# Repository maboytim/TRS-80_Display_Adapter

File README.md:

# TRS-80_Display_Adapter
Display board and CRT replacement for TRS-80 Models 3 and 4 and the big Tandy's.

### Overview

The adapter board connects to where the the display board normally connects.  It converts the video signals to HDMI or VGA so a modern monitor can be used instead of the builtin CRT.  The adapter uses a low cost (~$15) Nano-9k FPGA module.

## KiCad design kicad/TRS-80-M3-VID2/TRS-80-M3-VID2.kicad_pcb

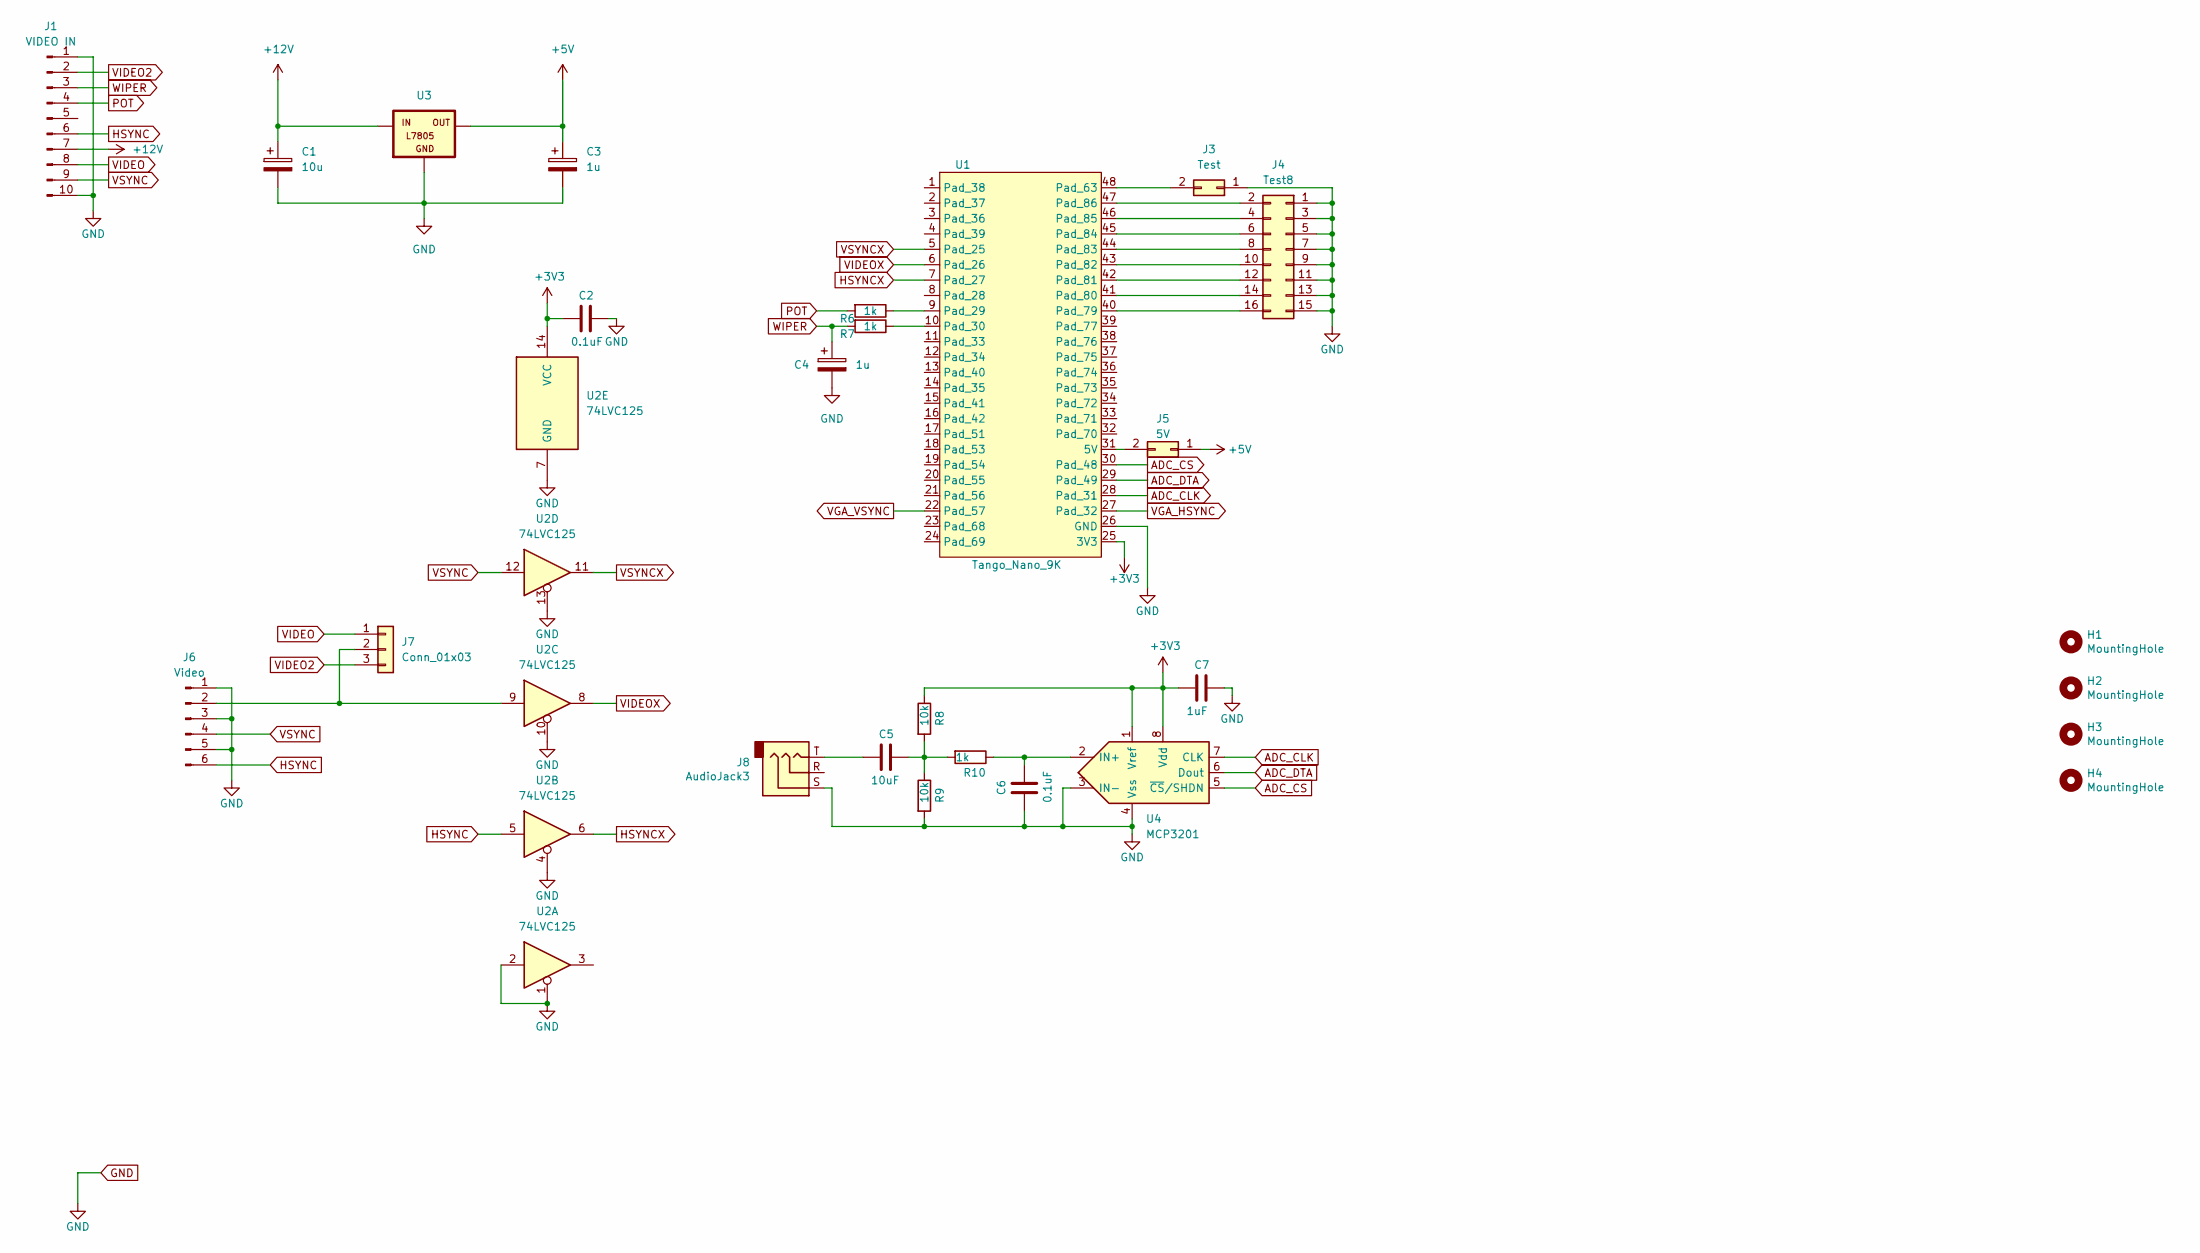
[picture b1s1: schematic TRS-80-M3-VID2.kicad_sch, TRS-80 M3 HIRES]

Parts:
C1: 10u; C_1206_3216Metric_Pad1.33x1.80mm_HandSolder
C2, C6: 0.1uF; C_0805_2012Metric_Pad1.18x1.45mm_HandSolder
C3, C4: 1u; C_1206_3216Metric_Pad1.33x1.80mm_HandSolder
C5: 10uF; C_0805_2012Metric_Pad1.18x1.45mm_HandSolder
C7: 1uF; C_0805_2012Metric_Pad1.18x1.45mm_HandSolder
H1, H2, H3, H4: MountingHole; MountingHole_3mm_Pad_Via
J1: VIDEO IN; TRSVID10
J3: Test; PinHeader_1x02_P2.54mm_Vertical
J4: Test8; PinSocket_2x08_P2.54mm_Vertical
J5: 5V; PinHeader_1x02_P2.54mm_Vertical
J6: Video; PinHeader_1x06_P2.54mm_Vertical
J7: Conn_01x03; PinHeader_1x03_P2.54mm_Vertical
J8: AudioJack3; Jack_3.5mm_CUI_SJ1-3535NG_Horizontal
R6, R7, R10: 1k; R_0805_2012Metric_Pad1.20x1.40mm_HandSolder
R8, R9: 10k; R_0805_2012Metric_Pad1.20x1.40mm_HandSolder
U1: Tango_Nano_9K; DIP-48_W22.9mm
U2: 74LVC125; SO-14_3.9x8.65mm_P1.27mm
U3: L7805; 78XXL
U4: MCP3201; SOIC-8_3.9x4.9mm_P1.27mm

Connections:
+3V3: C2.2, C7.2, R8.1, U1.25 (3V3), U2.14 (VCC), U4.1 (Vref), U4.8 (Vdd)
+5V: C3.1, J5.1, U3.OUT
+12V: C1.1, J1.7, U3.IN
ADC_CLK: U1.28 (Pad_31), U4.7 (CLK)
ADC_CS: U1.30 (Pad_48), U4.5 (~CS/SHDN)
ADC_DTA: U1.29 (Pad_49), U4.6 (Dout)
GND: C1.2, C2.1, C3.2, C4.2, C6.2, C7.1, J1.1, J1.10, J3.1, J4.1, J4.3, J4.5, J4.7, J4.9, J4.11, J4.13, J4.15, J6.1, J6.3, J6.5, J8.S, R9.2, U1.26 (GND), U2.1, U2.2, U2.4, U2.7 (GND), U2.10, U2.13, U3.GND, U4.3 (IN-), U4.4 (Vss)
HSYNC: J1.6, J6.6, U2.5
HSYNCX: U1.7 (Pad_27), U2.6
unnamed: C5.1, R8.2, R9.1, R10.2
unnamed: C5.2, J8.T
unnamed: J3.2, U1.48 (Pad_63)
unnamed: J4.2, U1.47 (Pad_86)
unnamed: J4.4, U1.46 (Pad_85)
unnamed: J4.6, U1.45 (Pad_84)
unnamed: J4.8, U1.44 (Pad_83)
unnamed: J4.10, U1.43 (Pad_82)
unnamed: J4.12, U1.42 (Pad_81)
unnamed: J4.14, U1.41 (Pad_80)
unnamed: J4.16, U1.40 (Pad_79)
unnamed: J5.2, U1.31 (5V)
unnamed: J6.2, J7.2, U2.9
unnamed: R6.1, U1.9 (Pad_29)
unnamed: R7.1, U1.10 (Pad_30)
unnamed: C6.1, R10.1, U4.2 (IN+)
POT: J1.4, R6.2
VGA_HSYNC: U1.27 (Pad_32)
VGA_VSYNC: U1.22 (Pad_57)
VIDEO: J1.8, J7.1
VIDEO2: J1.2, J7.3
VIDEOX: U1.6 (Pad_26), U2.8
VSYNC: J1.9, J6.4, U2.12
VSYNCX: U1.5 (Pad_25), U2.11
WIPER: C4.1, J1.3, R7.2

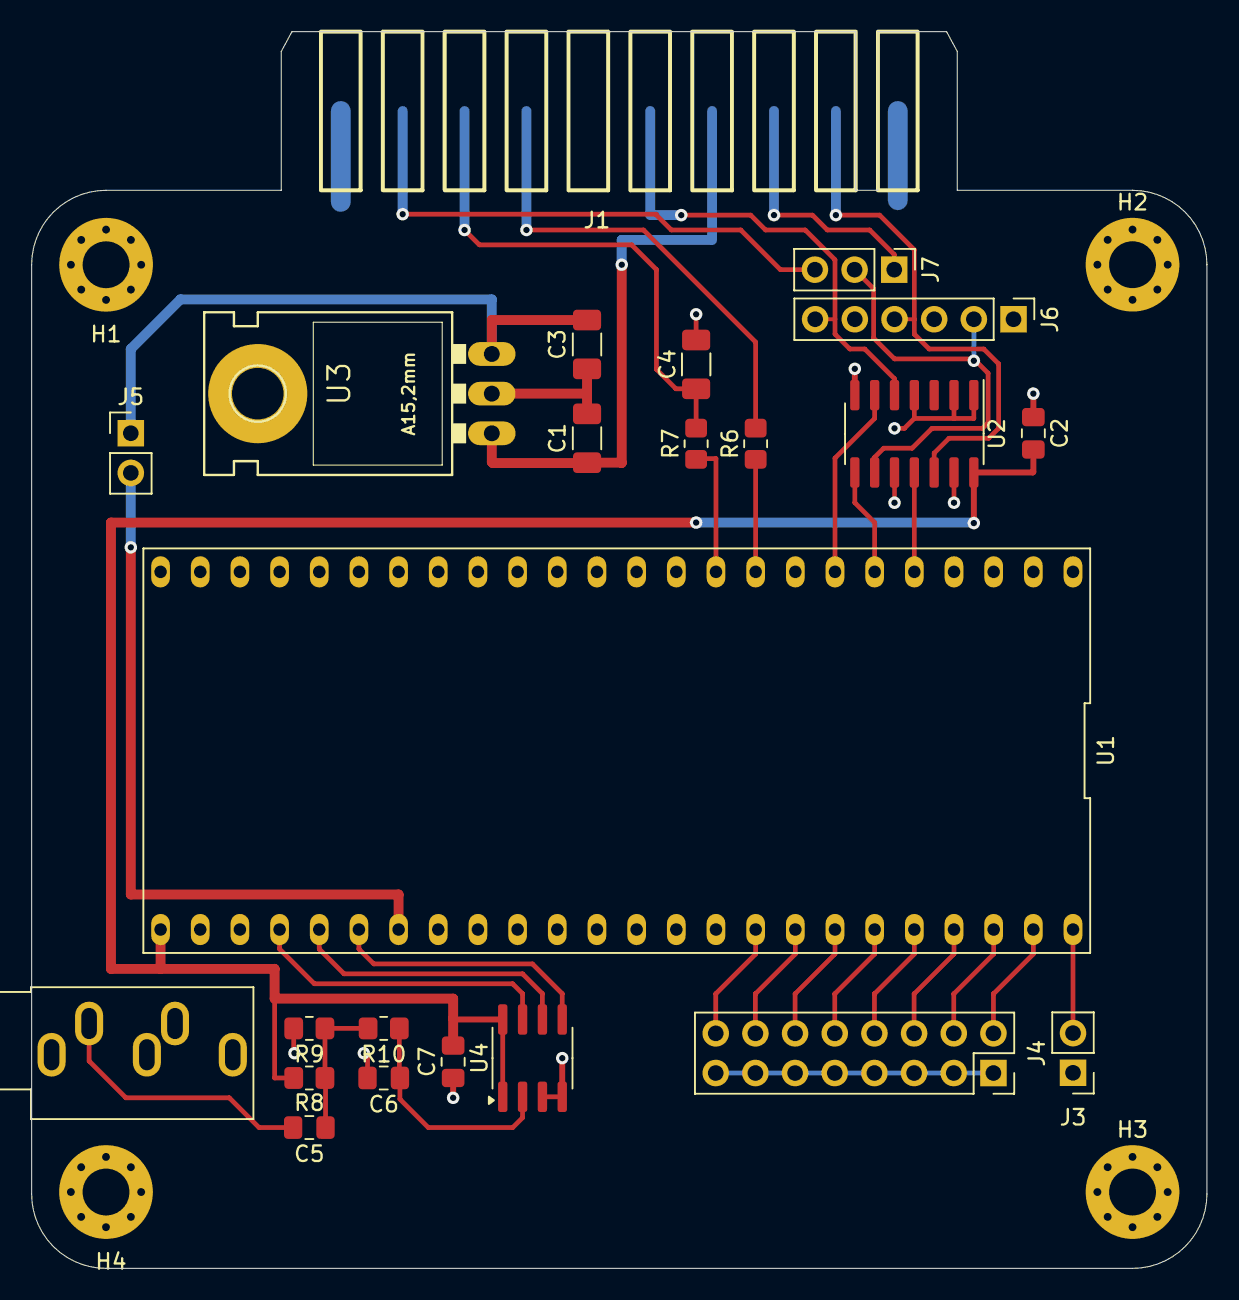
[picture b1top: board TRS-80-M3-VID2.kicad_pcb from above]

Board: 2 copper layers, 75.2 x 79.2 mm, 27 parts (0 on the bottom side), 32 nets.

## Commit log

2023-10-31 Added kicad project.
2023-10-31 Added pdf schematic.
2023-12-14 Added FPGA files for M3 version
2023-12-16 Added FPGA files for M4 version
2024-03-01 Added FPGA design for Big Tandy version.
2024-07-09 Added selection of 4 colors using two jumpers.
2024-12-14 Added FPGA design for Model 1 version.
2024-12-16 Added hardware support for cassette input to HDMI audio output.
2025-10-04 Added jumper option to BigTandy version for offsetting the display one column.
